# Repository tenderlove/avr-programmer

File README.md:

# My AVR Programmer

I've been messing around with an atmega328p and I kept finding myself building the same circuit on every breadboard.
In order to save time and breadboard space I decided to make an atmega328p breakout board.

This board works well with the [Sparkfun Pocket AVR programmer](https://www.sparkfun.com/products/9825).

Here is a photo:

## Parts list

* 1 [24 pin ZIF socket](https://www.aliexpress.com/item/32655076081.html)
* 1 [LD1117V33 voltage regulator](https://www.aliexpress.com/item/32892526691.html)
* 1 10uf capacitor
* 1 100nf capacitor
* 1 2N7000 MOSFET
* 1 [Mini USB B connector](https://www.digikey.com/product-detail/en/edac-inc/690-005-299-043/151-1206-1-ND/4312192)
* 1 [6 pin box header](https://www.digikey.com/product-detail/en/w-rth-elektronik/61200621621/732-5394-ND/4846913)
* 2 [15 pin 2.54mm headers](https://www.digikey.com/product-detail/en/sullins-connector-solutions/PPTC151LFBN-RC/S7013-ND/810153)

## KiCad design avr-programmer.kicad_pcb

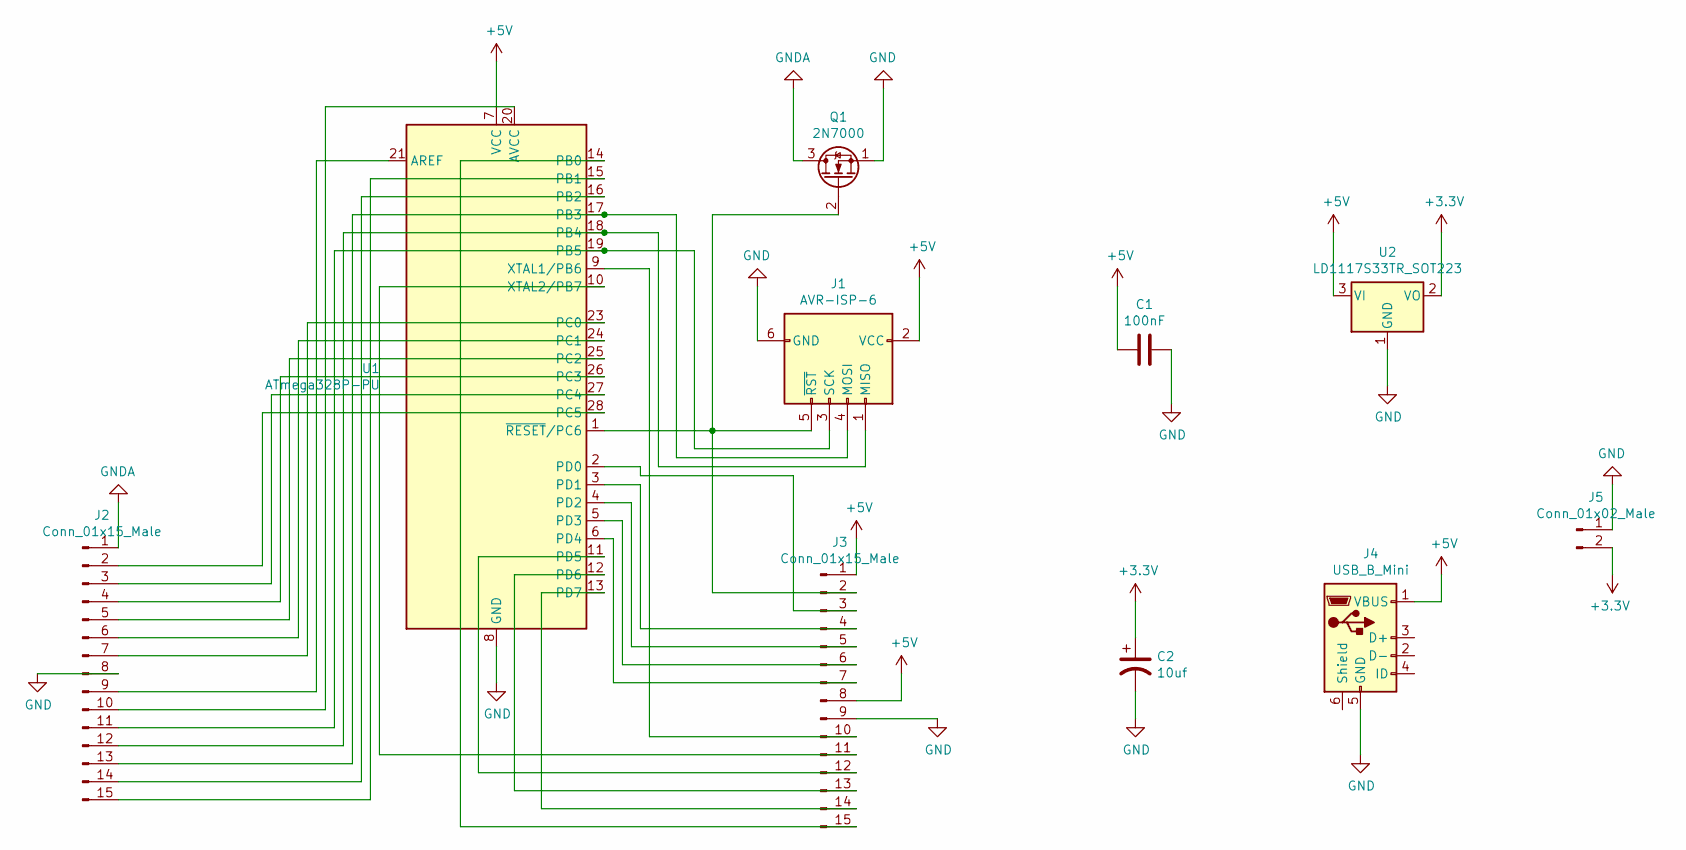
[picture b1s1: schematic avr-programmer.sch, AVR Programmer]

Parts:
C1: 100nF; C_Disc_D4.7mm_W2.5mm_P5.00mm
C2: 10uf; CP_Radial_D5.0mm_P2.00mm
J1: AVR-ISP-6; IDC-Header_2x03_P2.54mm_Vertical
J2, J3: Conn_01x15_Male; PinHeader_1x15_P2.54mm_Vertical
J4: USB_B_Mini; USB_Mini-B_Lumberg_2486_01_Horizontal
J5: Conn_01x02_Male; PinHeader_1x02_P2.54mm_Vertical
Q1: 2N7000; TO-92_Inline
U1: ATmega328P-PU; DIP-28_W7.62mm_ZIF
U2: LD1117S33TR_SOT223; TO-220-3_Horizontal_TabDown

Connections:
+3V3: C2.1, J5.2, U2.2 (VO)
+5V: C1.2, J1.2 (VCC), J3.1, J3.8, J4.1 (VBUS), U1.7 (VCC), U2.3 (VI)
GND: C1.1, C2.2, J1.6 (GND), J2.8, J3.9, J4.5 (GND), J5.1, Q1.1 (S), U1.8 (GND), U1.22 (GND), U2.1 (GND)
GNDA: J2.1, Q1.3 (D)
unnamed: J1.1 (MISO), J2.12, U1.18 (PB4)
unnamed: J1.3 (SCK), J2.11, U1.19 (PB5)
unnamed: J1.4 (MOSI), J2.13, U1.17 (PB3)
unnamed: J1.5 (~RST), J3.2, Q1.2 (G), U1.1 (~RESET~/PC6)
unnamed: J2.2, U1.28 (PC5)
unnamed: J2.3, U1.27 (PC4)
unnamed: J2.4, U1.26 (PC3)
unnamed: J2.5, U1.25 (PC2)
unnamed: J2.6, U1.24 (PC1)
unnamed: J2.7, U1.23 (PC0)
unnamed: J2.9, U1.21 (AREF)
unnamed: J2.10, U1.20 (AVCC)
unnamed: J2.14, U1.16 (PB2)
unnamed: J2.15, U1.15 (PB1)
unnamed: J3.3, U1.2 (PD0)
unnamed: J3.4, U1.3 (PD1)
unnamed: J3.5, U1.4 (PD2)
unnamed: J3.6, U1.5 (PD3)
unnamed: J3.7, U1.6 (PD4)
unnamed: J3.10, U1.9 (XTAL1/PB6)
unnamed: J3.11, U1.10 (XTAL2/PB7)
unnamed: J3.12, U1.11 (PD5)
unnamed: J3.13, U1.12 (PD6)
unnamed: J3.14, U1.13 (PD7)
unnamed: J3.15, U1.14 (PB0)

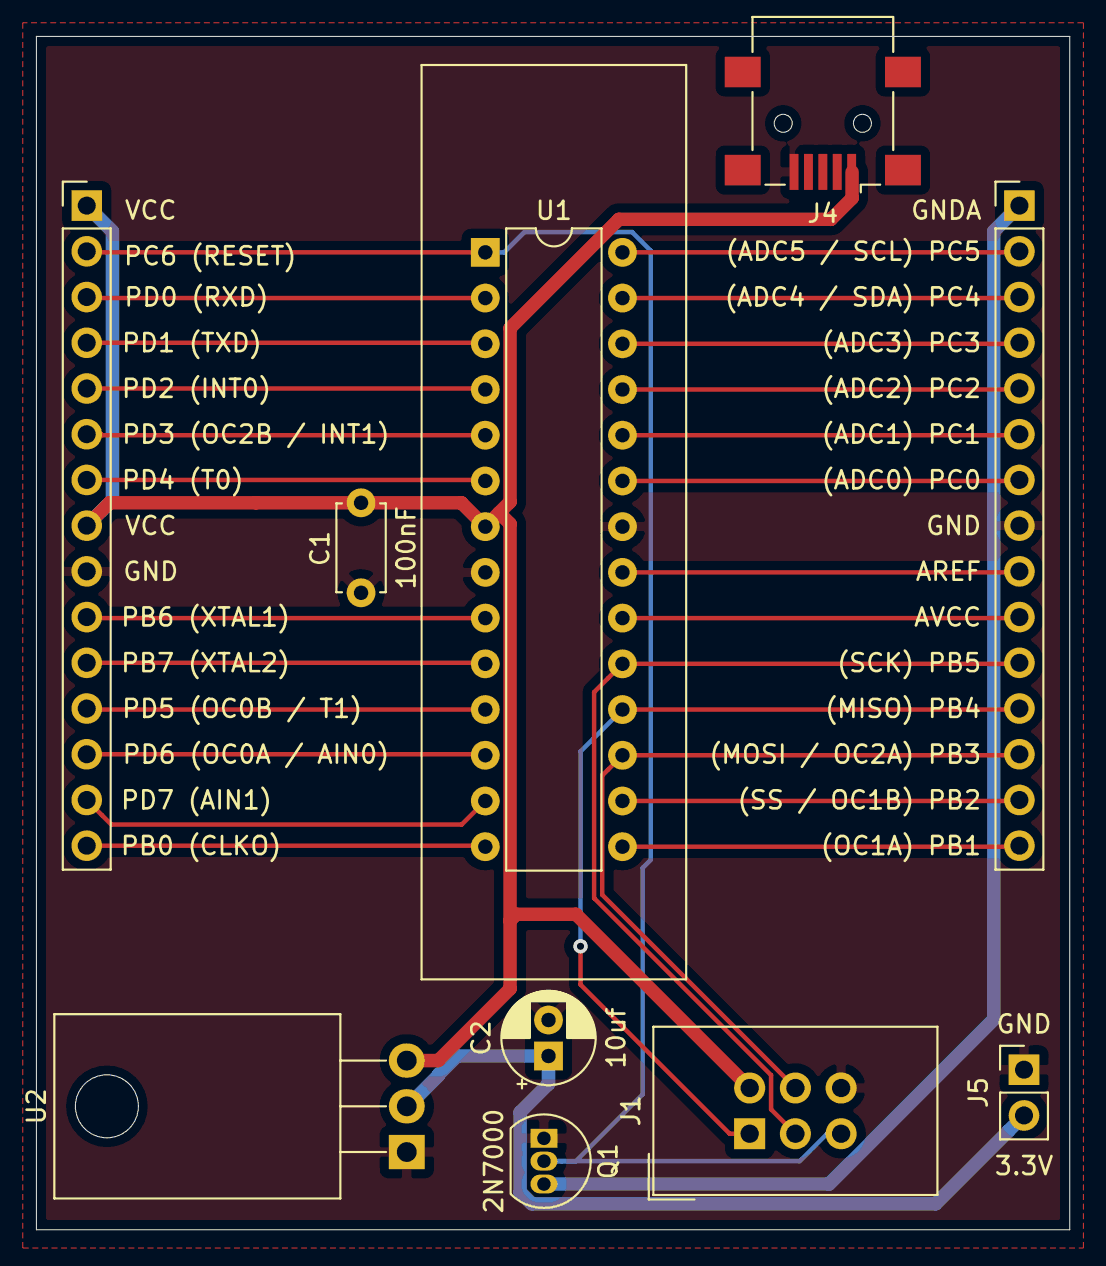
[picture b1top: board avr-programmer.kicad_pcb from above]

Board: 2 copper layers, 57.4 x 66.3 mm, 10 parts (0 on the bottom side), 29 nets.

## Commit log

2020-03-17 adding gitignore
2020-03-17 initial
2020-04-03 udating everything I guess!
2020-04-03 Create License
    anyone can use this for anything
2020-04-03 fix gerbers
2020-04-03 adding readme
